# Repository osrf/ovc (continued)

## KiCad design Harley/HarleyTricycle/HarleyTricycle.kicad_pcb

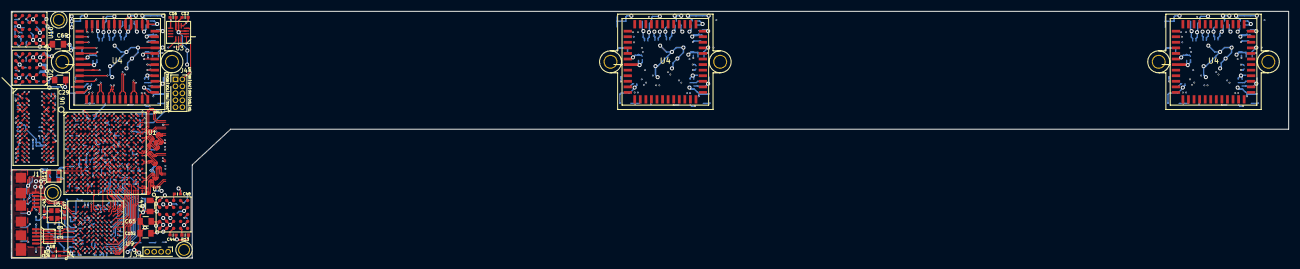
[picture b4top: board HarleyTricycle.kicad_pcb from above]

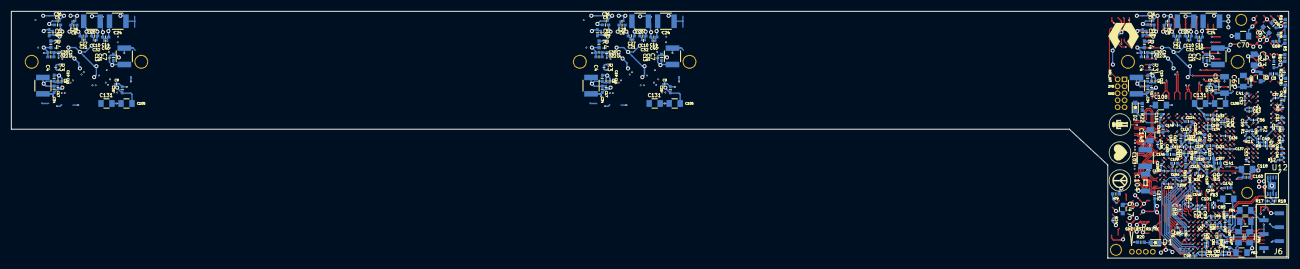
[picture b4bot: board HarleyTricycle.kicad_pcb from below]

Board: 10 copper layers, 233.0 x 45.0 mm, 277 parts (245 on the bottom side), 187 nets.

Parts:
C1, C3, C12, C16, C44, C48, C66, C68: 100n; C_0402
C2, C47, C67: 10u; C_0603
C4, C4#2, C4#3, C7, C7#2, C7#3, C20, C20#2, C20#3, C24, C24#2, C24#3: 100u; C_1210
C5, C5#2, C5#3, C8, C8#2, C8#3, C10, C10#2, C10#3, C14, C14#2, C14#3, C19, C19#2, C19#3, C22, C22#2, C22#3, C25, C25#2, C25#3, C27, C27#2, C27#3, C30, C30#2, C30#3, C31, C31#2, C31#3, C34, C34#2, C34#3, C39, C39#2, C39#3, C106, C107, C109, C110, C113, C114, C127, C129, C132, C133, C141, C142, C143, C145, C152, C154: 4.7u; C_0402
C6, C6#2, C6#3, C9, C9#2, C9#3, C11, C11#2, C11#3, C15, C15#2, C15#3, C46, C50, C52, C71, C72, C73, C75, C76, C77, C78, C79, C80, C81, C83, C84, C85, C86, C87, C88, C89, C93, C125: 100n; C_0201
C13, C13#2, C13#3, C17, C17#2, C17#3, C18, C18#2, C18#3, C21, C21#2, C21#3, C23, C28, C28#2, C28#3, C32, C32#2, C32#3, C36, C36#2, C36#3, C40, C40#2, C40#3, C58: 1u; C_0201
C26, C38, C42, C62, C63, C91, C92, C94, C95, C96, C97, C98, C99, C100, C101, C138, C139, C140: 10n; C_0201
C29, C33, C64, C65, C69, C70, C105, C105#2, C105#3, C108, C118, C131, C131#2, C131#3, C148: 47u; C_0805
C35: 10u; C_1206
C37, C41, C45, C49, C51, C53: 2.2n; C_0201
C43, C57: 15p; C_0402
C54, C56, C60, C111, C112, C115, C116, C117, C119, C120, C121, C122, C123, C124, C128, C130, C134, C135, C136, C137, C144, C146, C147, C149, C150, C151, C153, C155, C156, C157, C158, C159, C161: 470n; C_0201
C55: 3.3n; C_0201
C59: 4.7n; C_0201
C61, C74, C82, C102: 22u; C_0805
C90: 2.2u; C_0402
C103: 330u; C_1210
C104: 100u; C_1206
C126: 4.7n; C_0402
C160: 10n; C_0402
D1: GREEN; LED_0603
D2: RED; LED_0603
FB1, FB2, FB3, FB4: 600; C_0805
FB5, FB6: 600; C_0201
J1: USB_3.1_microB; USB3_Micro-B
J3: CONN_01X04; Pin_Header_Straight_1x04_Pitch1.27mm
J4: CONN_02X05; Pin_Header_Straight_2x05_Pitch1.27mm
J6: CONN_01X06; GRPB061VWTC
R1, R19, R21: 4.7k; C_0201
R2: 80.6; C_0201
R3, R3#2, R3#3: 100; C_0201
R4, R4#2, R4#3: 1k; R_0402
R5: 13.3k; R_0402
R6, R7: 1k; C_0201
R8: 48.7k; R_0402
R9: 19.1k; R_0402
R10: 90.9k; R_0402
R11: 240; C_0201
R12: 2k; C_0201
R13: 60.4k; R_0402
R14: 30.1k; R_0402
R15: 6.04k; C_0201
R16: 200; C_0201
R17, R18: 10k; C_0201
R20, R22: 200; R_0402
R23: 1M; C_0201
R24, R25, R26: R; C_0201
U1: xc7a100tcsg324pkg; BGA324C80P18X18_1500X1500X150
U2, U7, U10: LTM4622; LGA25_6.25X6.25X1.82
U3: ST_LSM6DS3; LGA14_2.5X3X0.86
U4, U4#2, U4#3: NOIP1SN1300A-QDI; LCC101.6P1422X1422X165-48
U5: 8y-19.200MAAE; 8y
U6: MT41K128M16; WBGA96C80P6X16_80X1400X110
U8: IC10pins; 10-UFDFN
U9: CYUSB3014; BGA121C80P11X11_1000X1000X110
U11: OSCILLATOR; ASDMB
U12: 24LC128T-I/MNY; 8-TDFN_2x3_1EP

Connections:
+1V0: C33.2, C103.1, C104.1, C107.1, C110.1, C111.1, C113.1, C120.1, C121.1, C122.1, C123.1, C124.1, C127.1, C129.1, C130.1, C161.1, U1.F8, U1.F10, U1.G7, U1.G9, U1.G11, U1.H8, U1.J7, U1.J11, U1.K8, U1.L7, U1.L11, U1.M8, U1.M10, U1.N7, U1.N9, U1.N11, U2.D1, U2.E1
+1V2: C65.2, C76.1, C78.1, C81.1, C84.1, C86.1, C89.1, C92.1, C95.1, C98.1, C100.1, C102.1, FB1.1, FB2.1, FB3.1, U7.D1, U7.E1, U9.B10, U9.C3, U9.E9, U9.F11, U9.H1, U9.J11, U9.L5, U9.L7
+1V8: C6.1, C6#2.1, C6#3.1, C9.1, C9#2.1, C9#3.1, C11.1, C11#2.1, C11#3.1, C15.1, C15#2.1, C15#3.1, C16.1, C19.1, C19#2.1, C19#3.1, C22.1, C22#2.1, C22#3.1, C25.1, C25#2.1, C25#3.1, C30.1, C30#2.1, C30#3.1, C35.1, C70.2, C105.1, C105#2.1, C105#3.1, C106.1, C109.1, C112.1, C115.1, C117.1, C119.1, FB6.1, U1.F12, U1.H12, U1.K12, U1.M12, U3.8, U4.6, U4.22, U4.26, U4#2.6, U4#2.22, U4#2.26, U4#3.6, U4#3.22, U4#3.26, U10.D1, U10.E1
+2V5: C64.2, C75.1, C77.1, C80.1, C83.1, C85.1, C88.1, C91.1, C94.1, C97.1, C99.1, C101.1, C118.1, C141.1, C142.1, C143.1, C144.1, C145.1, C146.1, C147.1, C148.1, C149.1, C150.1, C151.1, C152.1, C153.1, C154.1, C155.1, C156.1, C157.1, C158.1, C159.1, C160.1, FB4.1, J4.4, J6.5, R17.1, R18.1, R19.1, R20.1, R21.1, R22.1, U1.A17, U1.C13, U1.D16, U1.G15, U1.H18, U1.K4, U1.K14, U1.L17, U1.N3, U1.N13, U1.P6, U1.P8, U1.P11, U1.P12, U1.P13, U1.P16, U1.R9, U1.T2, U1.T12, U1.U5, U1.U15, U1.V8, U1.V18, U7.A1, U7.B1, U9.B1, U9.C11, U9.E3, U9.F1, U9.H4, U9.H11, U9.L9, U11.1, U11.4, U12.8
+3V3: C4.1, C4#2.1, C4#3.1, C5.1, C5#2.1, C5#3.1, C7.1, C7#2.1, C7#3.1, C8.1, C8#2.1, C8#3.1, C10.1, C10#2.1, C10#3.1, C12.1, C13.1, C13#2.1, C13#3.1, C14.1, C14#2.1, C14#3.1, C17.1, C17#2.1, C17#3.1, C18.1, C18#2.1, C18#3.1, C20.1, C20#2.1, C20#3.1, C21.1, C21#2.1, C21#3.1, C24.1, C24#2.1, C24#3.1, C27.1, C27#2.1, C27#3.1, C28.1, C28#2.1, C28#3.1, C31.1, C31#2.1, C31#3.1, C32.1, C32#2.1, C32#3.1, C34.1, C34#2.1, C34#3.1, C36.1, C36#2.1, C36#3.1, C39.1, C39#2.1, C39#3.1, C40.1, C40#2.1, C40#3.1, C69.2, C108.1, C114.1, C128.1, U1.B10, U3.5, U4.1, U4.19, U4.29, U4.31, U4.33, U4.36, U4.38, U4.40, U4#2.1, U4#2.19, U4#2.29, U4#2.31, U4#2.33, U4#2.36, U4#2.38, U4#2.40, U4#3.1, U4#3.19, U4#3.29, U4#3.31, U4#3.33, U4#3.36, U4#3.38, U4#3.40, U10.A1, U10.B1
+5V: C2.2, C47.2, C67.2, J1.1, U2.A2, U2.B2, U2.B3, U2.D2, U2.D3, U2.E2, U7.A2, U7.B2, U7.B3, U7.D2, U7.D3, U7.E2, U9.E10, U9.E11, U10.A2, U10.B2, U10.B3, U10.D2, U10.D3, U10.E2
/Sheet56A15E50/AVDDQ: C87.1, C90.1, FB3.2, U9.A7
/Sheet56A15E50/CVDDQ: C93.1, C96.1, FB4.2, U9.B6
/Sheet56A15E50/USB_SS_TX+: C72.2, U9.A5
/Sheet56A15E50/USB_SS_TX-: C71.2, U9.A6
/Sheet56A15E50/VDDRX: C79.1, C82.1, FB2.2, U9.A2
/Sheet56A15E50/VDDTX: C73.1, C74.1, FB1.2, U9.B5
/Sheet56A15EBD/GND_ADC: FB5.1, U1.H9, U1.J9, U1.K10
Artix_FX3_CLK: U1.P3, U9.J6
CAM_CLK_IN+: R3.2, R3#2.2, R3#3.2, U1.B13, U4.24, U4#2.24, U4#3.24
CAM_CLK_IN-: R3.1, R3#2.1, R3#3.1, U1.B14, U4.23, U4#2.23, U4#3.23
CAM_CLK_OUT+: U1.F15, U4.8, U4#2.8, U4#3.8
CAM_CLK_OUT-: U1.F16, U4.7, U4#2.7, U4#3.7
CAM_CLK_PLL: U1.C10, U4.25, U4#2.25, U4#3.25
CAM_DOUT0+: U1.A11, U4.10, U4#2.10, U4#3.10
CAM_DOUT0-: U1.B11, U4.9, U4#2.9, U4#3.9
CAM_DOUT1+: U1.A14, U4.12, U4#2.12, U4#3.12
CAM_DOUT1-: U1.A13, U4.11, U4#2.11, U4#3.11
CAM_DOUT2+: U1.A16, U4.14, U4#2.14, U4#3.14
CAM_DOUT2-: U1.A15, U4.13, U4#2.13, U4#3.13
CAM_DOUT3+: U1.B17, U4.16, U4#2.16, U4#3.16
CAM_DOUT3-: U1.B16, U4.15, U4#2.15, U4#3.15
CAM_RST#: U1.B9, U4.46, U4#2.46, U4#3.46
CAM_SS#: U1.A8, U4.47, U4#2.47, U4#3.47
CAM_SYNC+: U1.B18, U4.18, U4#2.18, U4#3.18
CAM_SYNC-: U1.A18, U4.17, U4#2.17, U4#3.17
CAM_monitor0: U1.A10, U4.44, U4#2.44, U4#3.44
CAM_monitor1: J4.1, U4.45, U4#2.45, U4#3.45
CAM_trigger0: U1.D10, U4.41, U4#2.41, U4#3.41
CAM_trigger1: U1.D9, U4.42, U4#2.42, U4#3.42
CAM_trigger2: U4.43, U4#2.43, U4#3.43
DDR_A0: U1.G2, U6.N3
DDR_A1: U1.H5, U6.P7
DDR_A2: U1.G3, U6.P3
DDR_A3: U1.H2, U6.N2
DDR_A4: U1.J4, U6.P8
DDR_A5: U1.J2, U6.P2
DDR_A6: U1.G6, U6.R8
DDR_A7: U1.K1, U6.R2
DDR_A8: U1.H6, U6.T8
DDR_A9: U1.J3, U6.R3
DDR_A10: U1.F6, U6.L7
DDR_A11: U1.H4, U6.R7
DDR_A12: U1.G4, U6.N7
DDR_A13: U1.K2, U6.T3
DDR_BA0: U1.E1, U6.M2
DDR_BA1: U1.G1, U6.N8
DDR_BA2: U1.F1, U6.M3
DDR_CAS#: U1.C1, U6.K3
DDR_CKE: R1.1, U1.H1, U6.K9
DDR_CLK+: R2.1, U1.F4, U6.J7
DDR_CLK-: R2.2, U1.F3, U6.K7
DDR_DQL0: U1.B7, U6.E3
DDR_DQL1: U1.D8, U6.F7
DDR_DQL2: U1.C7, U6.F2
DDR_DQL3: U1.B6, U6.F8
DDR_DQL4: U1.E5, U6.H3
DDR_DQL5: U1.D7, U6.H8
DDR_DQL6: U1.E6, U6.G2
DDR_DQL7: U1.E7, U6.H7
DDR_DQSL+: U1.A6, U6.F3
DDR_DQSL-: U1.A5, U6.G3
DDR_DQSU+: U1.B1, U6.C7
DDR_DQSU-: U1.A1, U6.B7
DDR_DQU0: U1.B2, U6.D7
DDR_DQU1: U1.D4, U6.C3
DDR_DQU2: U1.B3, U6.C8
DDR_DQU3: U1.D5, U6.C2
DDR_DQU4: U1.B4, U6.A7
DDR_DQU5: U1.C4, U6.A2
DDR_DQU6: U1.A3, U6.B8
DDR_DQU7: U1.A4, U6.A3
DDR_ODT: U1.E2, U6.K1
DDR_RAS#: U1.C2, U6.J3
DDR_RST#: R12.2, U1.J5, U6.T2
DDR_VDD: C29.2, C37.1, C38.1, C41.1, C42.1, C45.1, C46.1, C49.1, C50.1, C51.1, C52.1, C53.1, C54.1, C55.1, C56.1, C58.1, C59.1, C60.1, C61.1, C62.1, C63.1, C131.1, C131#2.1, C131#3.1, C132.1, C133.1, C134.1, C135.1, C136.1, C137.1, C138.1, C139.1, C140.1, R6.1, R12.1, U1.A7, U1.C3, U1.D6, U1.F2, U1.G5, U1.J1, U2.A1, U2.B1, U6.A1, U6.A8, U6.B2, U6.C1, U6.C9, U6.D2, U6.D9, U6.E9, U6.F1, U6.G7, U6.H2, U6.H9, U6.K2, U6.K8, U6.N1, U6.N9, U6.R1, U6.R9
DDR_VREF: C23.1, C26.1, R6.2, R7.1, U6.H1, U6.M8
DDR_WE#: U1.D2, U6.L3
FLASH_SCL: R18.2, U9.D10, U12.6
FLASH_SDA: R17.2, U9.D9, U12.5
FPGADebug1: J4.7, U1.C16
FPGADebug2: J4.9, U1.F14
FPGA_CLK: U1.N5, U11.3
FPGA_JTAG_TCK: J4.3, U1.E10
FPGA_JTAG_TDI: J4.10, U1.E11
FPGA_JTAG_TDO: J4.8, U1.E13
FPGA_JTAG_TMS: J4.5, U1.E12
FPGA_LED: D2.1, U1.C17
FPGA_SS_CCLK: U1.E9, U9.D2
FPGA_SS_DIN: U1.K18, U9.D1
FPGA_SS_DONE: U1.P10, U9.C4
FPGA_SS_DOUT: U1.T16, U9.C1
FPGA_SS_INIT_B: R19.2, U1.P7, U9.D3
FPGA_SS_PROGRAM_B: R21.2, U1.P9, U9.D4
FX3_A0: U1.T9, U9.H5
FX3_A1: U1.R11, U9.J5
FX3_DQ0: U1.V7, U9.F10
FX3_DQ1: U1.R3, U9.F9
FX3_DQ2: U1.R2, U9.F7
FX3_DQ3: U1.V4, U9.G10
FX3_DQ4: U1.T4, U9.G9
FX3_DQ5: U1.T3, U9.F8
FX3_DQ6: U1.V9, U9.H10
FX3_DQ7: U1.U6, U9.H9
FX3_DQ8: U1.V10, U9.J10
FX3_DQ9: U1.V11, U9.J9
FX3_DQ10: U1.U11, U9.K11
FX3_DQ11: U1.U13, U9.L10
FX3_DQ12: U1.V12, U9.K10
FX3_DQ13: U1.V14, U9.K9
FX3_DQ14: U1.T10, U9.J8
FX3_DQ15: U1.T5, U9.G8
FX3_DQ16: U1.U16, U9.K2
FX3_DQ17: U1.U12, U9.J4
FX3_DQ18: U1.V17, U9.K1
FX3_DQ19: U1.T14, U9.J2
FX3_DQ20: U1.V16, U9.J3
FX3_DQ21: U1.P14, U9.J1
FX3_DQ22: U1.R12, U9.H2
FX3_DQ23: U1.T11, U9.H3
FX3_DQ24: U1.P5, U9.F4
FX3_DQ25: U1.T13, U9.G2
FX3_DQ26: U1.R8, U9.G3
FX3_DQ27: U1.L14, U9.F3
FX3_DQ28: U1.U4, U9.F5
FX3_DQ29: U1.P18, U9.E1
FX3_DQ30: U1.V1, U9.E5
FX3_DQ31: U1.R16, U9.E4
FX3_FLAGA: U1.V6, U9.G7
FX3_FLAGB: U1.U9, U9.G6
FX3_FLAGC: U1.T15, U9.K6
FX3_FLAGD: U1.T8, U9.G5
FX3_JTAG_TCK: J6.1, U9.F6
FX3_JTAG_TDI: J6.2, U9.E7
FX3_JTAG_TDO: J6.4, U9.C10
FX3_JTAG_TMS: J6.3, U9.E8
FX3_LED/DEBUG: D1.1, U9.F2
FX3_PKT_END#: U1.R5, U9.H8
FX3_RST#: J3.2, U9.C5
FX3_SLCS#: U1.U14, U9.K8
FX3_SLOE#: U1.R10, U9.J7
FX3_SLRD#: U1.R6, U9.H7
FX3_SLWR#: U1.V15, U9.K7
FX3_UART_RX: J3.3, U9.D5
FX3_UART_TX: J3.4, U9.C2
GND: C1.2, C2.1, C3.2, C4.2, C4#2.2, C4#3.2, C5.2, C5#2.2, C5#3.2, C6.2, C6#2.2, C6#3.2, C7.2, C7#2.2, C7#3.2, C8.2, C8#2.2, C8#3.2, C9.2, C9#2.2, C9#3.2, C10.2, C10#2.2, C10#3.2, C11.2, C11#2.2, C11#3.2, C12.2, C13.2, C13#2.2, C13#3.2, C14.2, C14#2.2, C14#3.2, C15.2, C15#2.2, C15#3.2, C16.2, C17.2, C17#2.2, C17#3.2, C18.2, C18#2.2, C18#3.2, C19.2, C19#2.2, C19#3.2, C20.2, C20#2.2, C20#3.2, C21.2, C21#2.2, C21#3.2, C22.2, C22#2.2, C22#3.2, C23.2, C24.2, C24#2.2, C24#3.2, C25.2, C25#2.2, C25#3.2, C26.2, C27.2, C27#2.2, C27#3.2, C28.2, C28#2.2, C28#3.2, C29.1, C30.2, C30#2.2, C30#3.2, C31.2, C31#2.2, C31#3.2, C32.2, C32#2.2, C32#3.2, C33.1, C34.2, C34#2.2, C34#3.2, C35.2, C36.2, C36#2.2, C36#3.2, C37.2, C38.2, C39.2, C39#2.2, C39#3.2, C40.2, C40#2.2, C40#3.2, C41.2, C42.2, C43.2, C44.2, C45.2, C46.2, C47.1, C48.2, C49.2, C50.2, C51.2, C52.2, C53.2, C54.2, C55.2, C56.2, C57.2, C58.2, C59.2, C60.2, C61.2, C62.2, C63.2, C64.1, C65.1, C66.2, C67.1, C68.2, C69.1, C70.1, C73.2, C74.2, C75.2, C76.2, C77.2, C78.2, C79.2, C80.2, C81.2, C82.2, C83.2, C84.2, C85.2, C86.2, C87.2, C88.2, C89.2, C90.2, C91.2, C92.2, C93.2, C94.2, C95.2, C96.2, C97.2, C98.2, C99.2, C100.2, C101.2, C102.2, C103.2, C104.2, C105.2, C105#2.2, C105#3.2, C106.2, C107.2, C108.2, C109.2, C110.2, C111.2, C112.2, C113.2, C114.2, C115.2, C116.2, C117.2, C118.2, C119.2, C120.2, C121.2, C122.2, C123.2, C124.2, C125.2, C126.2, C127.2, C128.2, C129.2, C130.2, C131.2, C131#2.2, C131#3.2, C132.2, C133.2, C134.2, C135.2, C136.2, C137.2, C138.2, C139.2, C140.2, C141.2, C142.2, C143.2, C144.2, C145.2, C146.2, C147.2, C148.2, C149.2, C150.2, C151.2, C152.2, C153.2, C154.2, C155.2, C156.2, C157.2, C158.2, C159.2, C160.2, C161.2, FB5.2, J1.5, J1.8, J3.1, J4.6, J6.6, R1.2, R4.2, R4#2.2, R4#3.2, R5.2, R7.2, R8.2, R9.2, R10.2, R11.2, R13.2, R14.2, R15.2, R16.2, R23.2, R24.2, R25.2, R26.2, U1.A2, U1.A12, U1.B5, U1.B15, U1.C8, U1.C18, U1.D1, U1.D11, U1.E4, U1.E8, U1.E14, U1.F7, U1.F9, U1.F11, U1.F17, U1.G8, U1.G10, U1.G12, U1.H3, U1.H7, U1.H11, U1.H13, U1.J6, U1.J8, U1.J10, U1.J12, U1.J16, U1.K7, U1.K9, U1.K11, U1.L2, U1.L8, U1.L9, U1.L10, U1.L12, U1.M5, U1.M7, U1.M9, U1.M11, U1.M15, U1.N8, U1.N10, U1.N12, U1.N18, U1.P1, U1.R4, U1.R14, U1.T7, U1.T17, U1.U10, U1.V3, U1.V13, U2.B5, U2.C1, U2.C2, U2.D5, U3.2, U3.3, U3.6, U3.7, U4.5, U4.20, U4.21, U4.27, U4.30, U4.32, U4.34, U4.35, U4.37, U4.39, U4.48, U4#2.5, U4#2.20, U4#2.21, U4#2.27, U4#2.30, U4#2.32, U4#2.34, U4#2.35, U4#2.37, U4#2.39, U4#2.48, U4#3.5, U4#3.20, U4#3.21, U4#3.27, U4#3.30, U4#3.32, U4#3.34, U4#3.35, U4#3.37, U4#3.39, U4#3.48, U5.2, U5.4, U6.A9, U6.B1, U6.B3, U6.B9, U6.D1, U6.D3, U6.D8, U6.E1, U6.E2, U6.E7, U6.E8, U6.F9, U6.G1, U6.G8, U6.G9, U6.J2, U6.J8, U6.L2, U6.M1, U6.M9, U6.P1, U6.P9, U6.T1, U6.T9, U7.B5, U7.C1, U7.C2, U7.D5, U8.3, U8.8, U9.A1, U9.A8, U9.B2, U9.B4, U9.B7, U9.B8, U9.B9, U9.D8, U9.E2, U9.E6, U9.G1, U9.G11, U9.K3, U9.K4, U9.L1, U9.L2, U9.L3, U9.L6, U9.L11, U10.B5, U10.C1, U10.C2, U10.D5, U11.2, U12.3, U12.4, U12.7, U12.EPAD
IMU_INT1: J4.2, U3.4
IMU_SS#: U1.C11, U3.12
unnamed: C1.1, U2.E3
unnamed: C3.1, U2.A3
unnamed: C43.1, U5.3, U9.C7
unnamed: C44.1, U7.E3
unnamed: C48.1, U7.A3
unnamed: C57.1, U5.1, U9.C6
unnamed: C66.1, U10.E3
unnamed: C68.1, U10.A3
unnamed: C116.1, C125.1, FB6.2, U1.H10
unnamed: C126.1, J1.SHLD, R23.1
unnamed: D1.2, R20.2
unnamed: D2.2, R22.2
unnamed: R4.1, R4#2.1, R4#3.1, U4.28, U4#2.28, U4#3.28
unnamed: R5.1, U10.A4
unnamed: R8.1, U2.A4
unnamed: R9.1, U7.A4
unnamed: R10.1, U2.E4
unnamed: R11.1, U6.L8
unnamed: R13.1, U7.E4
unnamed: R14.1, U10.E4
unnamed: R15.1, U9.C8
unnamed: R16.1, U9.B3
unnamed: R24.1, U7.C5
unnamed: R25.1, U2.C5
unnamed: R26.1, U10.C5
SPI_MISO: U1.A9, U3.1, U4.3, U4#2.3, U4#3.3
SPI_MOSI: U1.C9, U3.14, U4.2, U4#2.2, U4#3.2
SPI_SCK: U1.B8, U3.13, U4.4, U4#2.4, U4#3.4
SS_RX+: J1.10, U8.5, U8.6, U9.A3
SS_RX-: J1.9, U8.4, U8.7, U9.A4
SS_TX+: C72.1, J1.7, U8.2, U8.9
SS_TX-: C71.1, J1.6, U8.1, U8.10
USB_HS_D+: J1.3, U9.A9
USB_HS_D-: J1.2, U9.A10

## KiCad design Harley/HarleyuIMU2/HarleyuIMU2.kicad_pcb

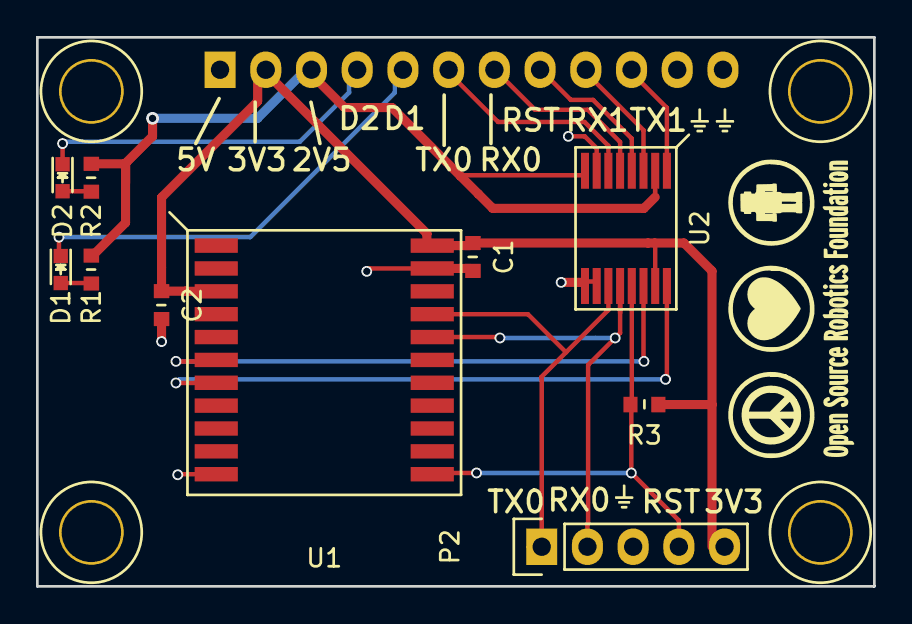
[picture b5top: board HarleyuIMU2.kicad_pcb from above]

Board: 2 copper layers, 46.5 x 30.5 mm, 11 parts (1 on the bottom side), 17 nets.

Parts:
C1, C2: 100n; C_0603
D1: GREEN; LED_0603
D2: RED; LED_0603
P1: CONN_01X12; Pin_Header_Straight_1x12
P2: CONN_01X05; Pin_Header_Straight_1x05
R1, R2: 200; R_0603
R3: 10k; R_0603
U1: uIMU-2; DFP-22_0.5mmPitch_125x155mm_HandSoldered
U2: TXB0106PWR; TSSOP-16_4.4x5mm_Pitch0.65mm_HandSoldered

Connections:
+2V5: P1.3, R1.1, R2.1, U2.2, U2.8
+3V3: C1.1, C2.1, P1.2, P2.5, R3.1, U1.3, U1.22, U2.15
FPGA_Signal1: D2.1, P1.4
FPGA_Signal2: D1.1, P1.5
GND: C1.2, C2.2, P1.11, P1.12, P2.3, U1.11, U1.21, U2.7, U2.9, U2.10
IMU_RST#: P2.4, R3.2, U1.12, U2.13
IMU_RST#_2V5: P1.8, U2.4
IMU_RX0: P2.2, U1.18, U2.12
IMU_RX0_2V5: P1.7, U2.5
IMU_RX1: U1.6, U2.14
IMU_RX1_2V5: P1.9, U2.3
IMU_TX0: P2.1, U1.19, U2.11
IMU_TX0_2V5: P1.6, U2.6
IMU_TX1: U1.7, U2.16
IMU_TX1_2V5: P1.10, U2.1
unnamed: D1.2, R1.2
unnamed: D2.2, R2.2

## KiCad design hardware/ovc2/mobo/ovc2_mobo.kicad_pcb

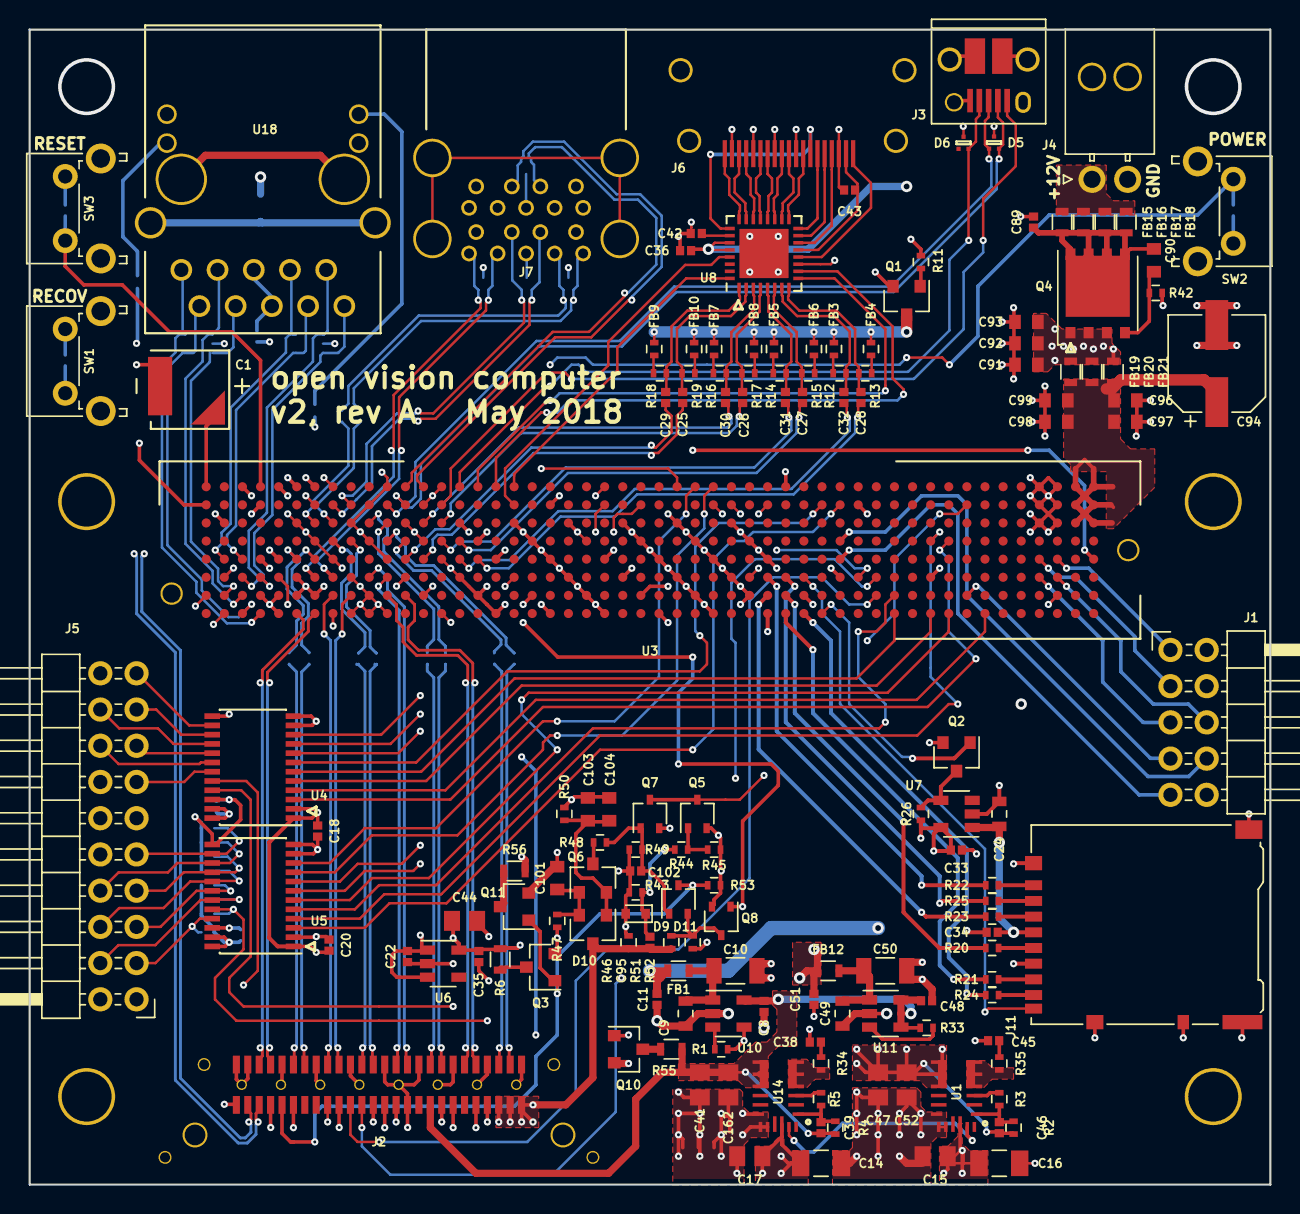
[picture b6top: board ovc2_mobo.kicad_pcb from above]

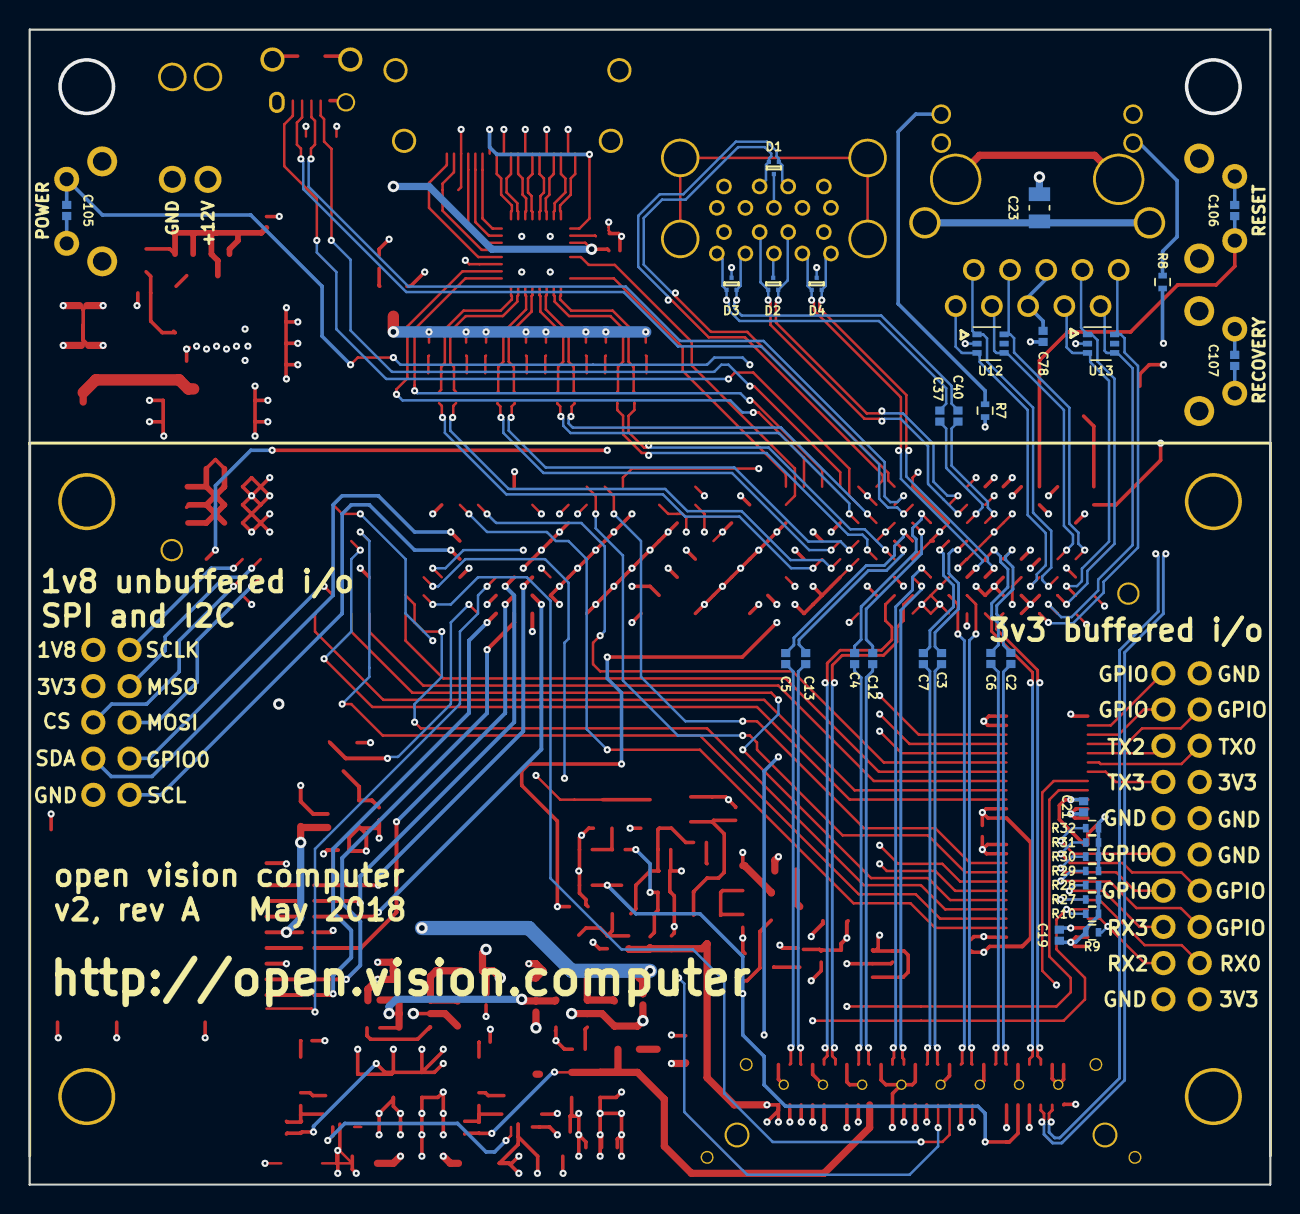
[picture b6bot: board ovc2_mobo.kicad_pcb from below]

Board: 6 copper layers, 87.0 x 81.0 mm, 181 parts (33 on the bottom side), 202 nets.

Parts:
C1: 80m; SEIKO_XH414HG_IV01E
C2, C3, C4, C5, C6, C7, C8, C11, C12, C13, C18, C19, C20, C21, C25, C26, C27, C28, C29, C30, C31, C32, C34, C36, C37, C40, C42, C48, C51, C89: 100n; C_0402_1005Metric
C9, C24, C49, C91, C92, C93, C96, C97, C98, C99, C103, C104: 10u; C_0603_1608Metric
C10, C50: 68u; C_1206_3216Metric
C14, C16: 22u; C_1206_3216Metric
C15, C17, C41, C44, C47, C52, C162: 22u; C_0805_2012Metric
C22, C33, C35, C43, C102: 1u; C_0402_1005Metric
C23: 100p; C_0805_2012Metric
C38, C45: 470p; C_0402_1005Metric
C39, C46: 22p; C_0402_1005Metric
C78: 10n; C_0402_1005Metric
C90: 4u7; C_0603_1608Metric
C94: 100u; CP_Elec_6.3x7.7
C95: 470n; C_0402_1005Metric
C101: 2u2; C_0603_1608Metric
C105, C106, C107: 1n; C_0402_1005Metric
D1, D2, D3, D4, D5, D6: TPD2EUSB30A; TPD2EUSB30x
D9: RB521S30T1G; D_SOD-523
D10: BAT54ALT1G; SOT-23
D11: BAT54CW-7-F; SOT-323_SC-70
FB1, FB12: 220; R_0603
FB3, FB4, FB5, FB6, FB7, FB8, FB9, FB10: 600; R_0402
FB15, FB16, FB17, FB18, FB19, FB20, FB21: 30; R_0603
J1: SPI/I2C; Pin_Header_Angled_2x05_Pitch2.54mm
J2: SAMTEC QRF8-RA; SAMTEC_QRF8-026-01-L-RA-GP
J3: USB_OTG; USB_Micro-B_10103594-0001LF
J4: POWER; Molex_NanoFit_1x02x2.50mm_Angled
J5: GPIO; Pin_Header_Angled_2x10_Pitch2.54mm
J6: HDMI_TYPE_A; AMP_FCI_10029449-111RLF_HDMI_TYPE_A
J7: USB; MOLEX_0484060003
J11: Micro_SD_Card_Det_Hirose_DM3AT; Hirose_DM3AT-SF-PEJM5
Q1: Q_NMOS_GSD; SOT-23
Q2: DMN2041L; SOT-23
Q3, Q10, Q11: NTR4003NT1G; SOT-23
Q4: AON6407; TDSON-8-1
Q5, Q7, Q8: NTS4001NT1G; SOT-323_SC-70
Q6: MMBT4403; SOT-23
R1, R9, R10, R11, R27, R28, R29, R30, R31, R32, R33, R42, R44, R46, R47, R48: 10k; R_0402
R2, R4, R34, R35: 51k; R_0402
R3: 11k3; R_0402
R5: 6k98; R_0402
R6, R56: 47; R_0603
R7, R8: 681; R_0402
R12, R13, R14, R15, R16, R17, R18, R19: 499; R_0402
R20: 0; R_0402
R21, R22, R23, R24, R25: 10; R_0402
R26, R45, R51: 47k; R_0402
R43, R49, R52, R53: 100k; R_0402
R50: 10M; R_0402
R55: 100; R_0603
SW1, SW2, SW3: SW_Push; SW_Tactile_SPST_Angled_PTS645Vx58-2LFS
U1, U14: MPM3630
U3: Jetson; JETSON_TX
U4, U5: SN74AVC8T245; TSSOP-24_4.4x7.8mm_Pitch0.65mm
U6: TLV733P; SOT-23-5
U7: NCP380LSN10AAT1G; SOT-23-5
U8: IP4786CZ32; QFN-32-1EP_5x5mm_Pitch0.5mm
U10, U11: TPS2069C; SOT-23-5
U12, U13: SP3002-04JTG; SOT-363_SC-70-6
U18: ARJ11C-MBSAS-A-BA-7MU2

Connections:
+1V8: C18.1, C20.1, C35.2, C36.1, C44.1, J1.2, R6.1, U4.1, U4.2, U5.1, U6.5, U8.27, U8.28
+3V3: C19.1, C21.1, C22.2, C33.1, C46.1, C47.1, C52.1, J1.4, J5.2, J5.14, R2.1, R9.1, R10.1, R11.1, R26.1, R27.1, R28.1, R56.1, U1.7, U1.8, U1.9, U4.23, U4.24, U5.23, U5.24, U6.1, U6.3, U7.5, U18.12, U18.13
+5V: C8.1, C39.1, C41.1, C48.1, C162.1, J2.18, R4.1, R33.1, R55.1, U8.11, U10.5, U11.4, U11.5, U14.7, U14.8, U14.9
+12V: C14.1, C15.1, C16.1, C17.1, C91.1, C92.1, C93.1, C95.1, D10.3, FB19.2, FB20.2, FB21.2, J2.2, J2.4, J2.6, Q4.1, Q4.2, Q4.3, R46.1, R51.1, U1.16, U14.16
/jetson_enet/GBE_MDI0+: U3.E48, U12.4, U18.8
/jetson_enet/GBE_MDI0-: U3.E49, U12.6, U18.7
/jetson_enet/GBE_MDI1+: U3.F47, U12.3, U18.10
/jetson_enet/GBE_MDI1-: U3.F48, U12.1, U18.9
/jetson_enet/GBE_MDI2+: U3.G48, U13.1, U18.3
/jetson_enet/GBE_MDI2-: U3.G49, U13.3, U18.4
/jetson_enet/GBE_MDI3+: U3.H47, U13.6, U18.1
/jetson_enet/GBE_MDI3-: U3.H48, U13.4, U18.2
/jetson_enet/LINK_1G: R8.1, U18.11
/jetson_enet/LINK_ACT: R7.1, U18.14
/jetson_hdmi/CEC: U3.B33, U8.29
/jetson_hdmi/CEC_CON: J6.13, U8.25
/jetson_hdmi/DDC_CLK: U3.A35, U8.9
/jetson_hdmi/DDC_CLK_CON: J6.15, U8.15
/jetson_hdmi/DDC_DAT: U3.A34, U8.10
/jetson_hdmi/DDC_DAT_CON: J6.16, U8.14
/jetson_hdmi/ESD_BYP: C42.1, U8.26
/jetson_hdmi/HDMI_TXC+: C32.2, U3.E36
/jetson_hdmi/HDMI_TXC-: C28.2, U3.E35
/jetson_hdmi/HDMI_TXD0+: C31.2, U3.D37
/jetson_hdmi/HDMI_TXD0-: C27.2, U3.D36
/jetson_hdmi/HDMI_TXD1+: C30.2, U3.C38
/jetson_hdmi/HDMI_TXD1-: C26.2, U3.C37
/jetson_hdmi/HDMI_TXD2+: C29.2, U3.E39
/jetson_hdmi/HDMI_TXD2-: C25.2, U3.E38
/jetson_hdmi/HPD: U3.A33, U8.32
/jetson_hdmi/HPDET_CON: J6.19, U8.12
/jetson_hdmi/TMDS_CON_CK+: J6.10, U8.18
/jetson_hdmi/TMDS_CON_CK-: J6.12, U8.17
/jetson_hdmi/TMDS_CON_D0+: J6.7, U8.20
/jetson_hdmi/TMDS_CON_D0-: J6.9, U8.19
/jetson_hdmi/TMDS_CON_D1+: J6.4, U8.22
/jetson_hdmi/TMDS_CON_D1-: J6.6, U8.21
/jetson_hdmi/TMDS_CON_D2+: J6.1, U8.24
/jetson_hdmi/TMDS_CON_D2-: J6.3, U8.23
/jetson_hdmi/TMDS_SYS_CK+: C32.1, R12.1, U8.7
/jetson_hdmi/TMDS_SYS_CK-: C28.1, R13.1, U8.8
/jetson_hdmi/TMDS_SYS_D0+: C31.1, R14.1, U8.5
/jetson_hdmi/TMDS_SYS_D0-: C27.1, R15.1, U8.6
/jetson_hdmi/TMDS_SYS_D1+: C30.1, R16.1, U8.3
/jetson_hdmi/TMDS_SYS_D1-: C26.1, R17.1, U8.4
/jetson_hdmi/TMDS_SYS_D2+: C29.1, R18.1, U8.1
/jetson_hdmi/TMDS_SYS_D2-: C25.1, R19.1, U8.2
/jetson_hdmi/UTILTY_CON: J6.14, U8.16
/jetson_pcie/PEX0_TX+: C6.2, U3.E44
/jetson_pcie/PEX0_TX-: C2.2, U3.E45
/jetson_pcie/PEX1_TX+: C7.2, U3.D42
/jetson_pcie/PEX1_TX-: C3.2, U3.D43
/jetson_pcie/PEX2_TX+: C12.2, U3.C40
/jetson_pcie/PEX2_TX-: C4.2, U3.C41
/jetson_pcie/PEX3_TX+: C13.2, U3.D39
/jetson_pcie/PEX3_TX-: C5.2, U3.D40
/jetson_power/POWER_BTN: C105.1, SW2.1, U3.B50
/jetson_power/RESET_IN: C106.1, SW3.1, U3.A47
/jetson_power/VDD_RTC: C1.1, U3.A50
/jetson_sdcard/SDCARD_CD: J11.9, U3.F17
/jetson_sdcard/SDCARD_CLK: J11.5, R20.1
/jetson_sdcard/SDCARD_CMD: J11.3, R23.1
/jetson_sdcard/SDCARD_D0: J11.7, R21.1
/jetson_sdcard/SDCARD_D1: J11.8, R24.1
/jetson_sdcard/SDCARD_D2: J11.1, R22.1
/jetson_sdcard/SDCARD_D3: J11.2, R25.1
/jetson_sdcard/SDCARD_PWR_EN: Q2.1, U3.H16
/jetson_sdcard/SDCARD_VDD: C24.1, C34.1, J11.4, U7.1
/jetson_usb/SS1_TX+: C37.2, U3.C43
/jetson_usb/SS1_TX-: C40.2, U3.C44
/jetson_usb/USB1_D+: D1.1, J7.3, U3.A38
/jetson_usb/USB1_D-: D1.2, J7.2, U3.A39
/jetson_usb/USB1_EN: R1.1, U3.A18, U10.4
/jetson_usb/USB1_VBUS: C11.1, FB1.2, J7.1
/power/DROP_DETECT: C102.1, D11.1, Q7.1, R48.2, R49.1
/power/VIN: FB15.2, FB16.2, FB17.2, FB18.2, J4.1
/power/~PWR_EN: D11.2, Q8.3, R51.2, R52.1
CONSOLE_RX_1V8: U3.G12, U5.5
CONSOLE_RX_3V3: J5.4, R27.2, U5.19
CONSOLE_TX_1V8: U3.H12, U4.6
CONSOLE_TX_3V3: J5.16, U4.18
DISCHARGE: D11.3, J2.44, Q3.1, Q10.1, Q11.1, R53.1
FPGA_CONFIG_DATA0: J2.30, U3.F13
FPGA_CONFIG_DCLK: J2.32, U3.G13
FPGA_CONF_DONE: J2.28, U3.B19
FPGA_NCONFIG: J2.24, U3.B22
FPGA_NSTATUS: J2.26, U3.B21
GND: C1.2, C8.2, C9.2, C10.2, C11.2, C14.2, C15.2, C16.2, C17.2, C18.2, C19.2, C20.2, C21.2, C22.1, C23.2, C24.2, C33.2, C34.2, C35.1, C36.2, C38.2, C41.2, C42.2, C43.2, C44.2, C45.2, C47.2, C48.2, C49.2, C50.2, C51.2, C52.2, C78.1, C89.2, C91.2, C92.2, C93.2, C94.2, C96.2, C97.2, C98.2, C99.2, C101.2, C102.2, C103.2, C104.2, C105.2, C106.2, C107.2, C162.2, D1.3, D2.3, D3.3, D4.3, D5.3, D6.3, D9.2, J1.10, J2.1, J2.7, J2.13, J2.19, J2.22, J2.25, J2.31, J2.34, J2.37, J2.43, J2.46, J2.49, J2.51, J2.52, J2.53, J2.54, J2.55, J2.56, J3.5, J3.6, J4.2, J5.1, J5.10, J5.11, J5.12, J5.20, J6.2, J6.5, J6.8, J6.11, J6.17, J6.20, J7.4, J7.7, J7.13, J7.16, J11.6, J11.10, J11.11, Q1.2, Q2.2, Q3.2, Q5.2, Q7.2, Q8.2, Q10.2, Q11.2, R29.1, R30.1, R31.1, R32.1, R42.2, R43.2, R45.2, R46.2, R47.2, R49.2, R50.2, R52.2, R53.2, SW1.2, SW2.2, SW3.2, U1.12, U1.13, U1.14, U3.A3, U3.A4, U3.A28, U3.A37, U3.A40, U3.A43, U3.B3, U3.B4, U3.B14, U3.B31, U3.B38, U3.B41, U3.B44, U3.B47, U3.C3, U3.C4, U3.C21, U3.C24, U3.C27, U3.C30, U3.C33, U3.C36, U3.C39, U3.C42, U3.C45, U3.D20, U3.D23, U3.D26, U3.D29, U3.D32, U3.D35, U3.D38, U3.D41, U3.D44, U3.E19, U3.E22, U3.E25, U3.E28, U3.E31, U3.E34, U3.E37, U3.E40, U3.E43, U3.E46, U3.F10, U3.F15, U3.F21, U3.F24, U3.F27, U3.F30, U3.F33, U3.F36, U3.F39, U3.F42, U3.F45, U3.F49, U3.G3, U3.G17, U3.G20, U3.G23, U3.G26, U3.G29, U3.G32, U3.G35, U3.G38, U3.G41, U3.G44, U3.G45, U3.G46, U3.G47, U3.G50, U3.H19, U3.H22, U3.H25, U3.H28, U3.H31, U3.H34, U3.H37, U3.H40, U3.H41, U3.H42, U3.H43, U3.H46, U3.H49, U4.11, U4.12, U4.13, U4.22, U5.2, U5.11, U5.12, U5.13, U5.22, U6.2, U7.2, U8.33, U10.2, U11.2, U12.2, U13.2, U14.12, U14.13, U14.14
GPIO0: J1.7, U3.G8
GPIO1_1V8: U3.F14, U5.7
GPIO1_3V3: J5.6, R29.2, U5.17
GPIO2_1V8: U3.F20, U5.8
GPIO2_3V3: J5.7, R30.2, U5.16
GPIO3_1V8: U3.A23, U5.10
GPIO3_3V3: J5.9, R32.2, U5.14
GPIO4_1V8: U3.A22, U5.9
GPIO4_3V3: J5.8, R31.2, U5.15
GPIO5_1V8: U3.A24, U4.10
GPIO5_3V3: J5.19, U4.14
GPIO6_1V8: U3.B26, U4.8
GPIO6_3V3: J5.18, U4.16
GPIO7_1V8: U3.B28, U4.9
GPIO7_3V3: J5.17, U4.15
HDMI_PULLDOWNS: Q1.1, R11.2
I2C0_SCL_1V8: J1.9, U3.E15
I2C0_SDA_1V8: J1.8, U3.D15
IMU_RX1_1V8: U3.D9, U4.3
IMU_RX1_3V3: J2.16, U4.21
IMU_TX1_1V8: U3.D10, U5.4
IMU_TX1_3V3: J2.14, R10.2, U5.20
JETSON_CARRIER_PWR_ON: J2.8, Q8.1, U1.17, U3.A48, U14.17
JETSON_PWR_BAD: Q5.3, Q7.3, U3.B8
JETSON_RESET_OUT: J2.10, U3.A46
JETSON_VDD_MOD: C94.1, C96.1, C97.1, C98.1, C99.1, FB19.1, FB20.1, FB21.1, U3.A1, U3.A2, U3.B1, U3.B2, U3.C1, U3.C2
LED: J2.36, U4.20
LED_1V8: U3.H7, U4.4
unnamed: C9.1, C10.1, FB1.1, U10.1
unnamed: C23.1, U18.SHLD
unnamed: C38.1, R34.1
unnamed: C39.2, R4.2, R5.1, U14.1
unnamed: C43.1, J6.18, U8.13
unnamed: C45.1, R35.1
unnamed: C46.2, R2.2, R3.1, U1.1
unnamed: C49.1, C50.1, FB12.1, U11.1
unnamed: C78.2, U18.5, U18.6
unnamed: C89.1, C90.1, FB15.1, FB16.1, FB17.1, FB18.1, Q4.5
unnamed: C90.2, Q4.4, R42.1
unnamed: C95.2, D9.1, R43.1, R44.1
unnamed: C101.1, D10.2, Q6.1, R47.1
unnamed: C103.1, C104.1, D10.1, Q6.2, R50.1
unnamed: C107.1, SW1.1, U3.E1
unnamed: FB3.1, R12.2
unnamed: FB4.1, R13.2
unnamed: FB5.1, R14.2
unnamed: FB6.1, R15.2
unnamed: FB7.1, R16.2
unnamed: FB8.1, R17.2
unnamed: FB9.1, R18.2
unnamed: FB10.1, R19.2
unnamed: FB3.2, FB4.2, FB5.2, FB6.2, FB7.2, FB8.2, FB9.2, FB10.2, Q1.3
unnamed: Q2.3, R26.2, U7.4
unnamed: Q3.3, R6.2
unnamed: Q5.1, R44.2, R45.1
unnamed: Q6.3, R48.1
unnamed: Q10.3, R55.2
unnamed: Q11.3, R56.2
unnamed: R1.2, U10.3
unnamed: R3.2, U1.3
unnamed: R5.2, U14.3
unnamed: R7.2, U3.E47
unnamed: R8.2, U3.F46
unnamed: R20.2, U3.G18
unnamed: R21.2, U3.H18
unnamed: R22.2, U3.F19
unnamed: R23.2, U3.G19
unnamed: R24.2, U3.H17
unnamed: R25.2, U3.F18
unnamed: R33.2, U11.3
unnamed: R34.2, U14.4, U14.5, U14.6
unnamed: R35.2, U1.4, U1.5, U1.6
PCIE_LANE0_RX+: J2.45, U3.H44
PCIE_LANE0_RX-: J2.47, U3.H45
PCIE_LANE0_TX+: C6.1, J2.39
PCIE_LANE0_TX-: C2.1, J2.41
PCIE_LANE1_RX+: J2.33, U3.G42
PCIE_LANE1_RX-: J2.35, U3.G43
PCIE_LANE1_TX+: C7.1, J2.27
PCIE_LANE1_TX-: C3.1, J2.29
PCIE_LANE2_RX+: J2.23, U3.F40
PCIE_LANE2_RX-: J2.21, U3.F41
PCIE_LANE2_TX+: C12.1, J2.17
PCIE_LANE2_TX-: C4.1, J2.15
PCIE_LANE3_RX+: J2.9, U3.G39
PCIE_LANE3_RX-: J2.11, U3.G40
PCIE_LANE3_TX+: C13.1, J2.5
PCIE_LANE3_TX-: C5.1, J2.3
PCIE_REFCLK+: J2.48, U3.A44
PCIE_REFCLK-: J2.50, U3.A45
PCIE_RST_3V3: J2.42, U3.C49
SPI0_CLK: J1.1, U3.E3
SPI0_CS: J1.6, U3.F3
SPI0_MISO: J1.3, U3.E4
SPI0_MOSI: J1.5, U3.F4
UART2_RX_1V8: U3.B15, U5.3
UART2_RX_3V3: J5.3, R9.2, U5.21
UART2_TX_1V8: U3.B16, U4.7
UART2_TX_3V3: J5.15, U4.17
UART3_RX_1V8: U3.H9, U5.6
UART3_RX_3V3: J5.5, R28.2, U5.18
UART3_TX_1V8: U3.H10, U4.5
UART3_TX_3V3: J5.13, U4.19
USB0_D+: D5.1, J3.3, U3.B39
USB0_D-: D5.2, J3.2, U3.B40
USB0_ID: D6.2, J3.4, U3.A36
USB0_VBUS: J3.1, U3.B37
USB1_SSRX+: D4.1, J7.15, U3.F43
USB1_SSRX-: D4.2, J7.14, U3.F44
USB1_SSTX+: C37.1, D3.1, J7.18
USB1_SSTX-: C40.1, D3.2, J7.17
USB2_5V_LIM: C51.1, FB12.2, J7.10
USB2_D+: D2.2, J7.12, U3.B42
USB2_D-: D2.1, J7.11, U3.B43
